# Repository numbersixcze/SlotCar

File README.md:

# SlotCar
School project - gyroscope driven slot car

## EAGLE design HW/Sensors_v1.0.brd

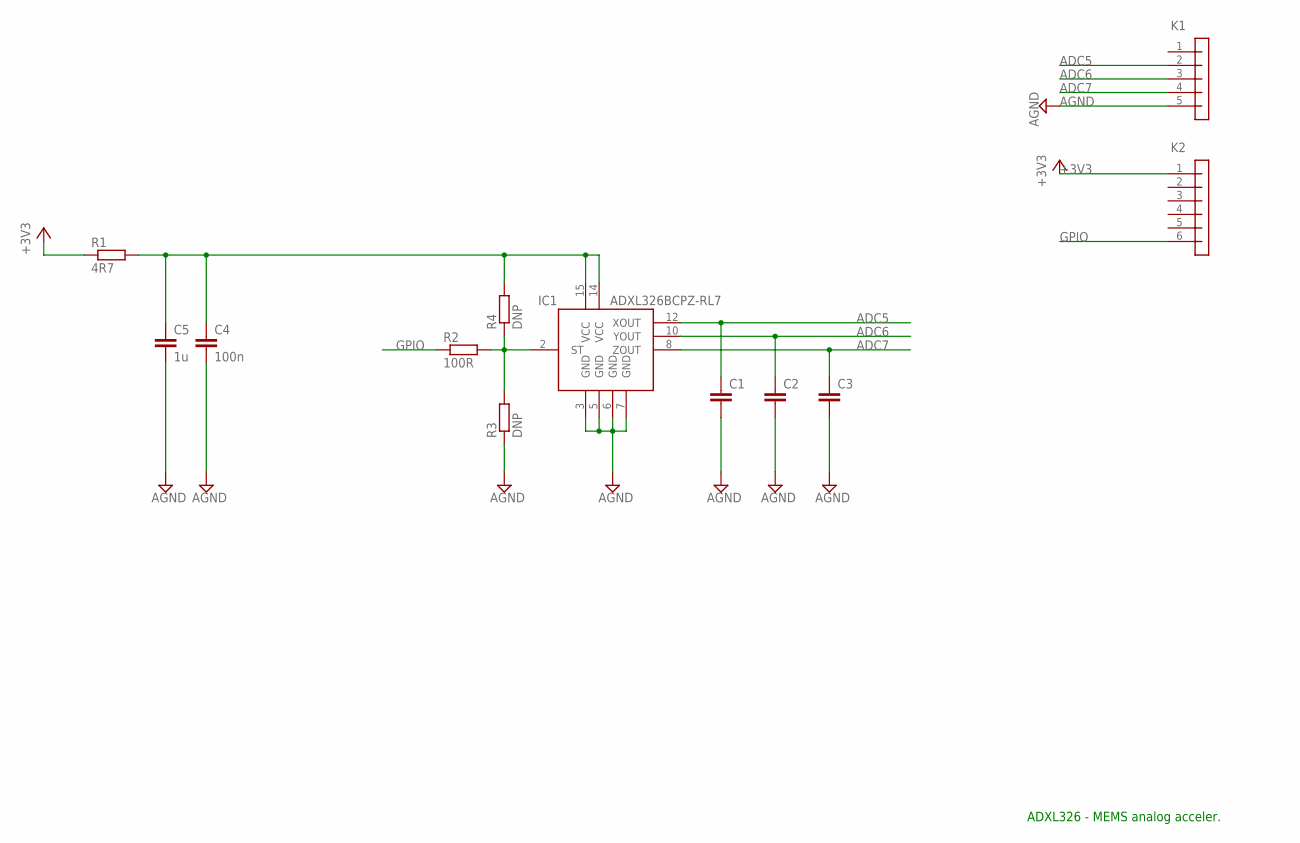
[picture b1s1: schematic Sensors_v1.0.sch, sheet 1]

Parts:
C1, C2, C3: C-EUC0805K; C0805K
C4: 100n; C0805K
C5: 1u; C0805K
IC1: ADXL326BCPZ-RL7; LFCSP-LQ-16
K1: PIN_1X5_1.27THT; PINHEAD_1X5_RM1.27THT
K2: PIN_1X6_1.27THT; PINHEAD_1X6_RM1.27THT
R1: 4R7; M0805
R2: 100R; M0805
R3, R4: DNP; M0805

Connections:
+3V3: K2.1, R1.1; also elsewhere on the board
ADC5: C1.1, IC1.12 (XOUT), K1.2; also elsewhere on the board
ADC6: C2.1, IC1.10 (YOUT), K1.3; also elsewhere on the board
ADC7: C3.1, IC1.8 (ZOUT), K1.4; also elsewhere on the board
AGND: C1.2, C2.2, C3.2, C4.2, C5.2, IC1.3 (GND), IC1.5 (GND), IC1.6 (GND), IC1.7 (GND), K1.5, R3.1; also elsewhere on the board
GPIO: K2.6, R2.1; also elsewhere on the board
unnamed: C4.1, C5.1, IC1.14 (VCC), IC1.15 (VCC), R1.2, R4.2
unnamed: IC1.2 (ST), R2.2, R3.2, R4.1

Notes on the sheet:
ADXL326 - MEMS analog acceler.

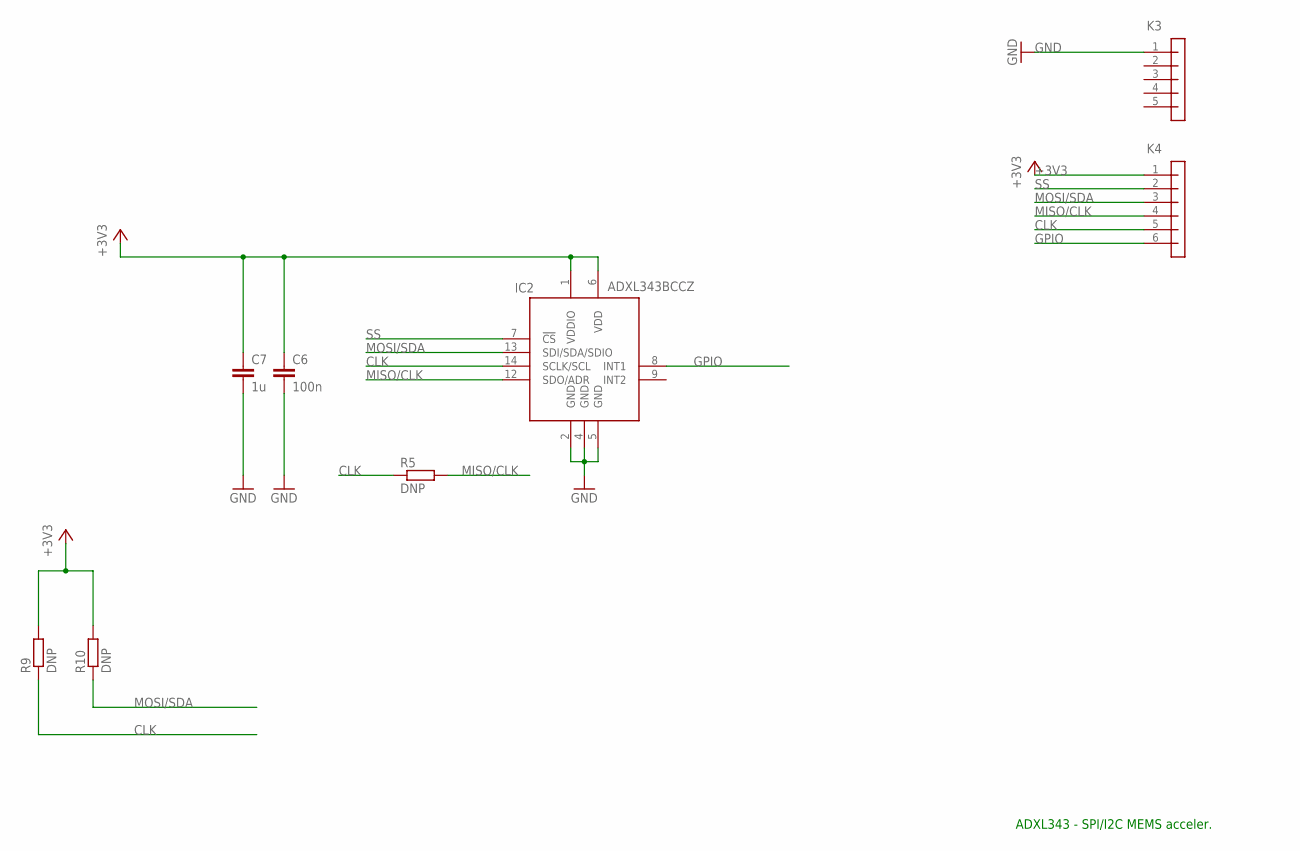
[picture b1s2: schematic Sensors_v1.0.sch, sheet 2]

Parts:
C6: 100n; C0805K
C7: 1u; C0805K
IC2: ADXL343BCCZ; LGA14(CC-14-1)
K3: PIN_1X5_1.27THT; PINHEAD_1X5_RM1.27THT
K4: PIN_1X6_1.27THT; PINHEAD_1X6_RM1.27THT
R5, R9, R10: DNP; M0805

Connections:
+3V3: C6.1, C7.1, IC2.1 (VDDIO), IC2.6 (VDD), K4.1, R9.2, R10.2; also elsewhere on the board
CLK: IC2.14 (SCLK/SCL), K4.5, R5.1, R9.1; also elsewhere on the board
GND: C6.2, C7.2, IC2.2 (GND), IC2.4 (GND), IC2.5 (GND), K3.1; also elsewhere on the board
GPIO: IC2.8 (INT1), K4.6; also elsewhere on the board
MISO/CLK: IC2.12 (SDO/ADR), K4.4, R5.2; also elsewhere on the board
MOSI/SDA: IC2.13 (SDI/SDA/SDIO), K4.3, R10.1; also elsewhere on the board
SS: IC2.7 (!CS), K4.2; also elsewhere on the board

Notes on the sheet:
ADXL343 - SPI/I2C MEMS acceler.

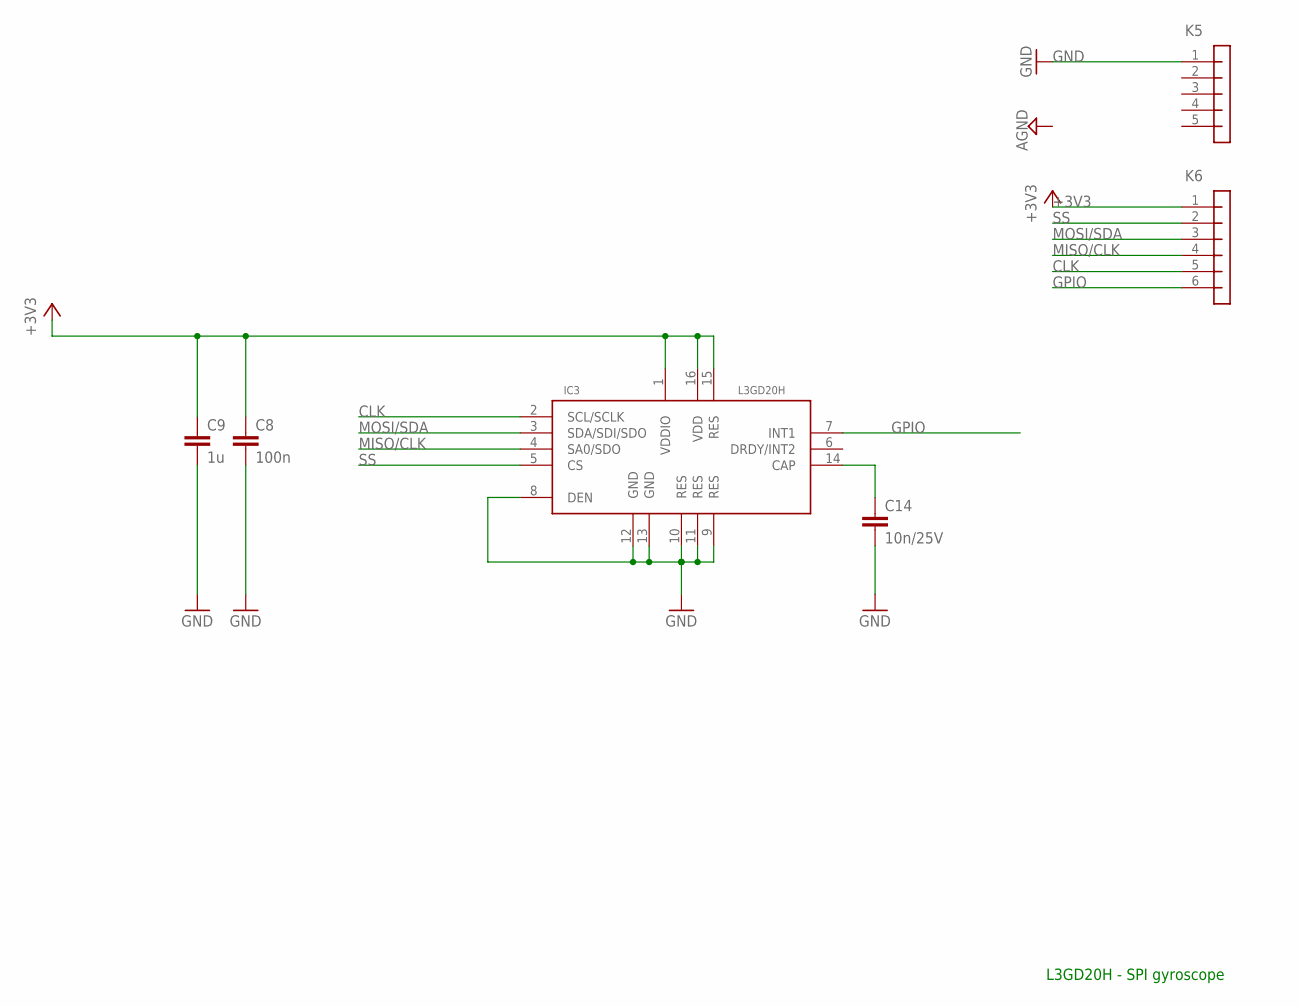
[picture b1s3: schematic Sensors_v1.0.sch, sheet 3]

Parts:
C8: 100n; C0805K
C9: 1u; C0805K
C14: 10n/25V; C0805K
IC3: L3GD20H; LGA16L
K5: PIN_1X5_1.27THT; PINHEAD_1X5_RM1.27THT
K6: PIN_1X6_1.27THT; PINHEAD_1X6_RM1.27THT

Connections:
+3V3: C8.1, C9.1, IC3.1 (VDDIO), IC3.15 (RES), IC3.16 (VDD), K6.1; also elsewhere on the board
CLK: IC3.2 (SCL/SCLK), K6.5; also elsewhere on the board
GND: C8.2, C9.2, C14.2, IC3.8 (DEN), IC3.9 (RES), IC3.10 (RES), IC3.11 (RES), IC3.12 (GND), IC3.13 (GND), K5.1; also elsewhere on the board
GPIO: IC3.7 (INT1), K6.6; also elsewhere on the board
MISO/CLK: IC3.4 (SA0/SDO), K6.4; also elsewhere on the board
MOSI/SDA: IC3.3 (SDA/SDI/SDO), K6.3; also elsewhere on the board
unnamed: C14.1, IC3.14 (CAP)
SS: IC3.5 (CS), K6.2; also elsewhere on the board

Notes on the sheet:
L3GD20H - SPI gyroscope

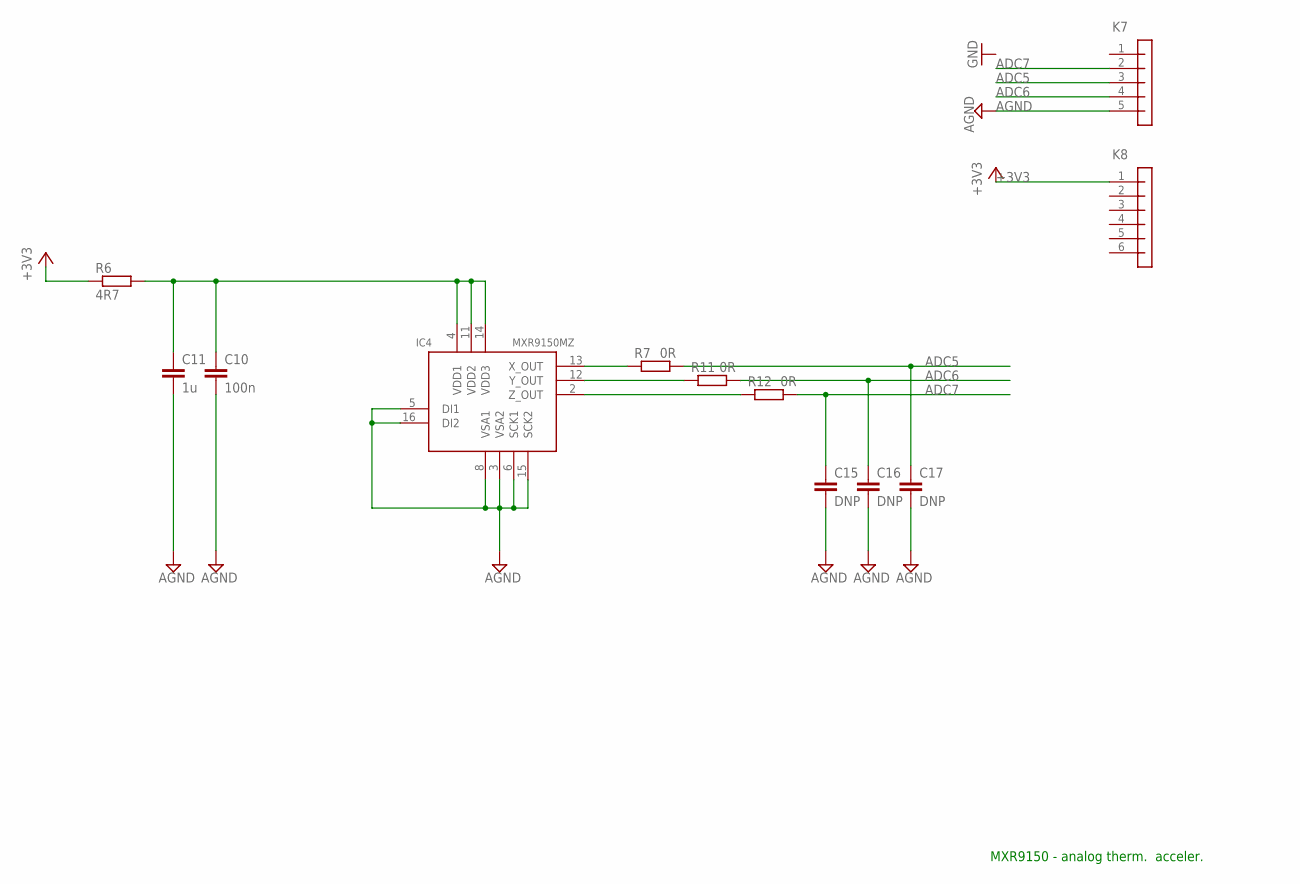
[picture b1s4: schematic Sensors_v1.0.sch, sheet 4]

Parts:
C10: 100n; C0805K
C11: 1u; C0805K
C15, C16, C17: DNP; C0805K
IC4: MXR9150MZ; LCC16
K7: PIN_1X5_1.27THT; PINHEAD_1X5_RM1.27THT
K8: PIN_1X6_1.27THT; PINHEAD_1X6_RM1.27THT
R6: 4R7; M0805
R7, R11, R12: 0R; M0805

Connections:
+3V3: K8.1, R6.1; also elsewhere on the board
ADC5: C17.1, K7.3, R7.2; also elsewhere on the board
ADC6: C16.1, K7.4, R11.2; also elsewhere on the board
ADC7: C15.1, K7.2, R12.2; also elsewhere on the board
AGND: C10.2, C11.2, C15.2, C16.2, C17.2, IC4.3 (VSA2), IC4.5 (DI1), IC4.6 (SCK1), IC4.8 (VSA1), IC4.15 (SCK2), IC4.16 (DI2), K7.5; also elsewhere on the board
unnamed: C10.1, C11.1, IC4.4 (VDD1), IC4.11 (VDD2), IC4.14 (VDD3), R6.2
unnamed: IC4.13 (X_OUT), R7.1
unnamed: IC4.12 (Y_OUT), R11.1
unnamed: IC4.2 (Z_OUT), R12.1

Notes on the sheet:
MXR9150 - analog therm. acceler.

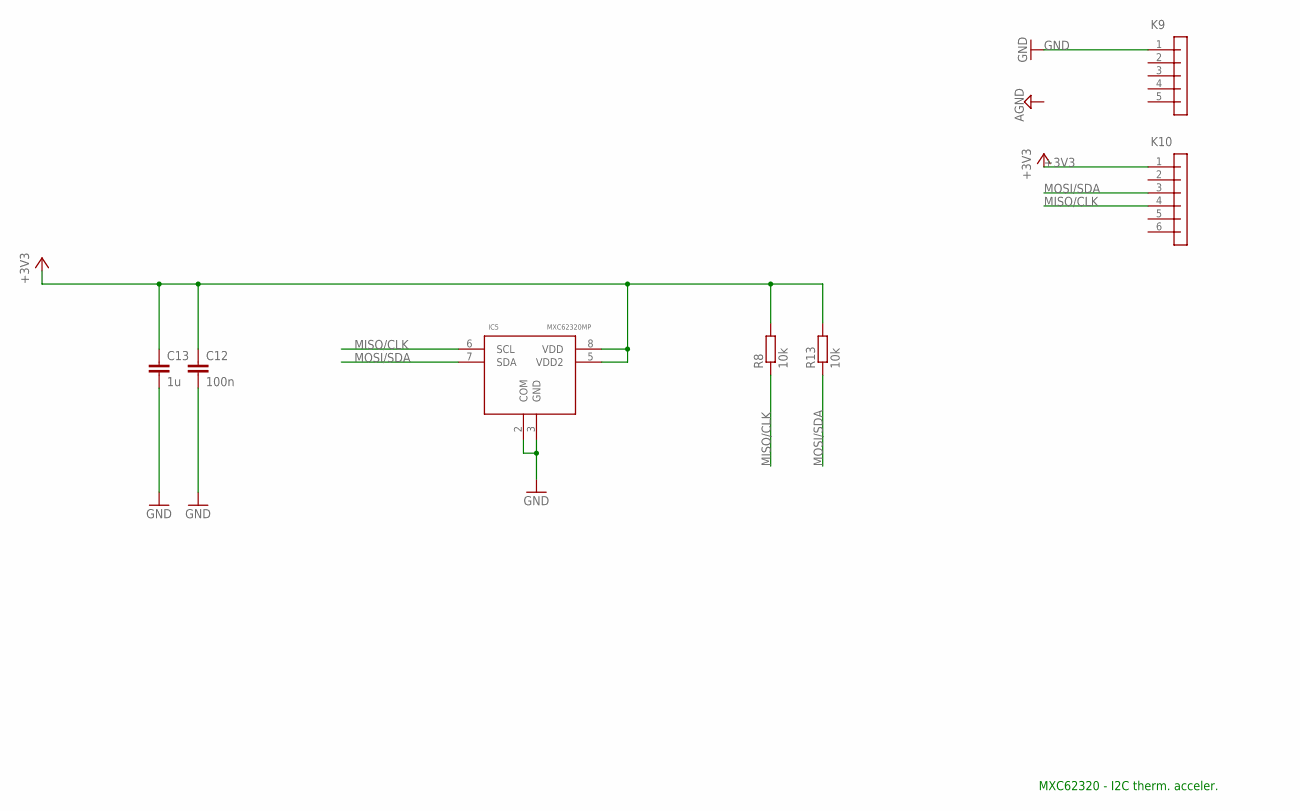
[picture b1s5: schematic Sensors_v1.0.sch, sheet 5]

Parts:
C12: 100n; C0805K
C13: 1u; C0805K
IC5: MXC62320MP; LCC8
K9: PIN_1X5_1.27THT; PINHEAD_1X5_RM1.27THT
K10: PIN_1X6_1.27THT; PINHEAD_1X6_RM1.27THT
R8, R13: 10k; M0805

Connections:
+3V3: C12.1, C13.1, IC5.5 (VDD2), IC5.8 (VDD), K10.1, R8.2, R13.2; also elsewhere on the board
GND: C12.2, C13.2, IC5.2 (COM), IC5.3 (GND), K9.1; also elsewhere on the board
MISO/CLK: IC5.6 (SCL), K10.4, R8.1; also elsewhere on the board
MOSI/SDA: IC5.7 (SDA), K10.3, R13.1; also elsewhere on the board

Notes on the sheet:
MXC62320 - I2C therm. acceler.

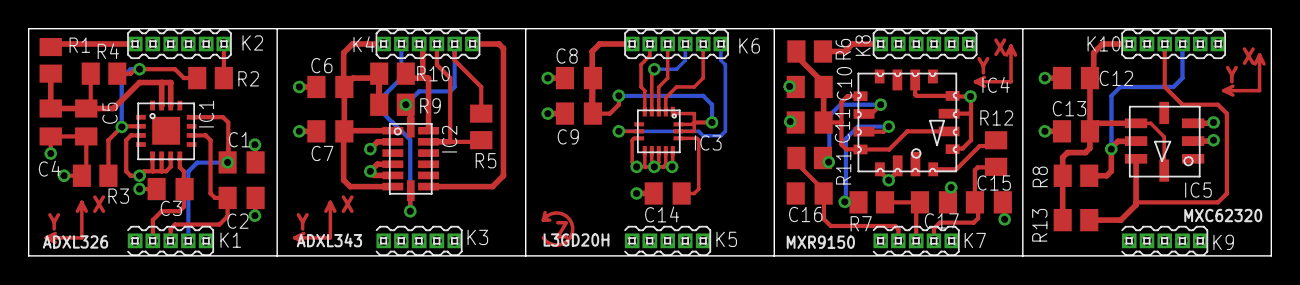
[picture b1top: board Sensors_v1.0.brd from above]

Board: 2 copper layers, 88.9 x 16.3 mm, 45 parts (0 on the bottom side), 18 nets.

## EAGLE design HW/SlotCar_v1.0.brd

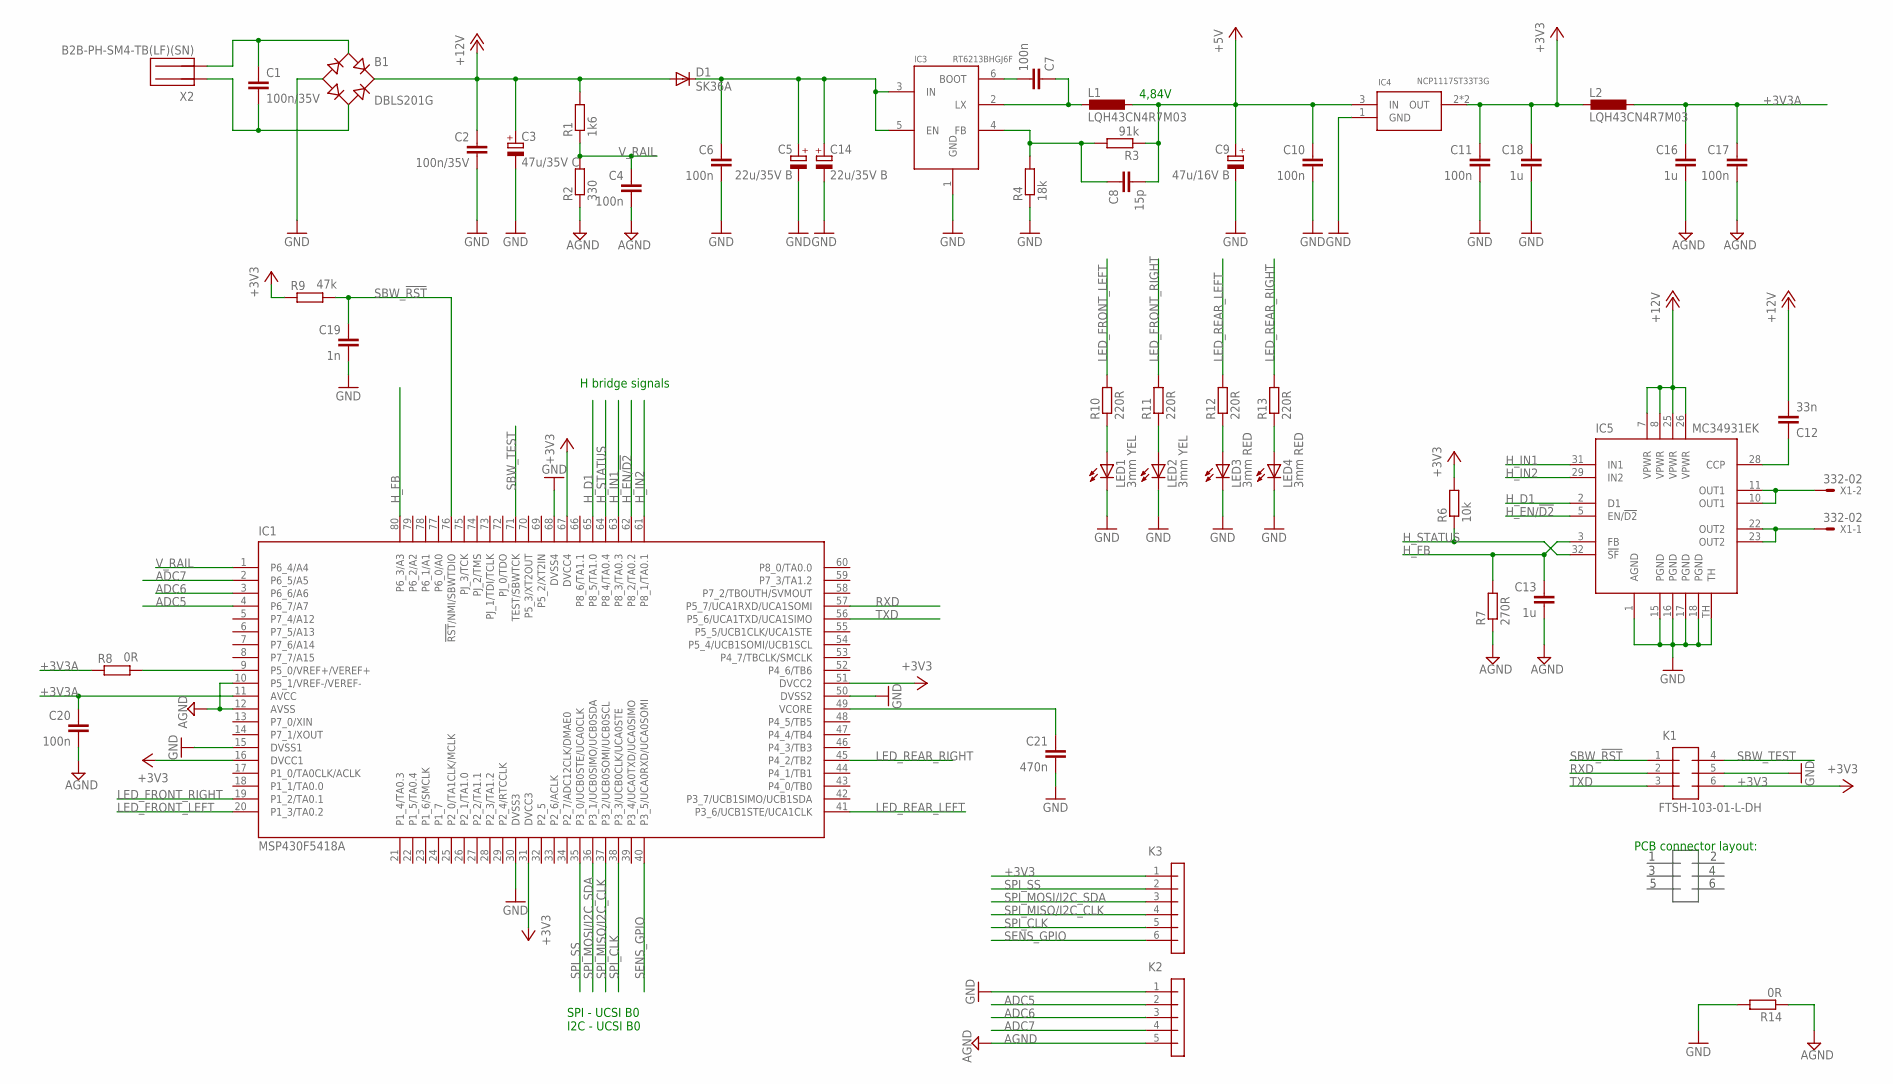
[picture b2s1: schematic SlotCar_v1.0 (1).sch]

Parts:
B1: DBLS201G; DBS
C1, C2: 100n/35V; C0805K
C3: 47u/35V C; 153CLV-0505
C4, C6, C7, C10, C11, C17, C20: 100n; C0805K
C5, C14: 22u/35V B; 153CLV-0405
C8: 15p; C0805K
C9: 47u/16V B; 153CLV-0405
C12: 33n; C0805K
C13, C16, C18: 1u; C0805K
C19: 1n; C0805K
C21: 470n; C0805K
D1: SK36A; DO214AC
IC1: MSP430F5418A; PN_S-PQFP-G80
IC3: RT6213BHGJ6F; SOT23-6
IC4: NCP1117ST33T3G; SOT223
IC5: MC34931EK; SOIC32W
K1: FTSH-103-01-L-DH; PINHEAD_2X3_RM1.27
K2: PIN_1X5_SMD; PINHEAD_1X5_RM1.27SMD
K3: PIN_1X6_SMD; PINHEAD_1X6_RM1.27SMD
L1, L2: LQH43CN4R7M03; L1812
LED1, LED2: 3mm YEL; LED3MM
LED3, LED4: 3mm RED; LED3MM
R1: 1k6; M0805
R2: 330; M0805
R3: 91k; M0805
R4: 18k; M0805
R6: 10k; M0805
R7: 270R; M0805
R8, R14: 0R; M0805
R9: 47k; M0805
R10, R11, R12, R13: 220R; M0805
X1: 332-02
X2: B2B-PH-SM4-TB(LF)(SN); JST-2.00MM-2P

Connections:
+3V3: C11.1, C18.1, IC1.16 (DVCC1), IC1.31 (DVCC3), IC1.51 (DVCC2), IC1.67 (DVCC4), IC4.2 (OUT), IC4.4 (OUT), K1.6, K3.1, L2.2, R6.2, R9.1
+3V3A: C16.1, C17.1, C20.1, IC1.11 (AVCC), L2.1, R8.1
+5V: C8.2, C9.+, C10.1, IC4.3 (IN), L1.1, R3.1
+12V: B1.+, C2.1, C3.+, C12.2, D1.A, IC5.7 (VPWR), IC5.8 (VPWR), IC5.25 (VPWR), IC5.26 (VPWR), R1.2
ADC5: IC1.4 (P6_7/A7), K2.2
ADC6: IC1.3 (P6_6/A6), K2.3
ADC7: IC1.2 (P6_5/A5), K2.4
AGND: C4.2, C13.2, C16.2, C17.2, C20.2, IC1.10 (P5_1/VREF-/VEREF-), IC1.12 (AVSS), K2.5, R2.1, R7.1, R14.1
GND: B1.-, C2.2, C3.-, C5.-, C6.2, C9.-, C10.2, C11.2, C14.-, C18.2, C19.2, C21.2, IC1.15 (DVSS1), IC1.30 (DVSS3), IC1.50 (DVSS2), IC1.68 (DVSS4), IC3.1 (GND), IC4.1 (GND), IC5.1 (AGND), IC5.15 (PGND), IC5.16 (PGND), IC5.17 (PGND), IC5.18 (PGND), IC5.TH, K1.5, K2.1, LED1.K (C), LED2.K (C), LED3.K (C), LED4.K (C), R4.1, R14.2
H_D1: IC1.65 (P8_5/TA1.0), IC5.2 (D1)
H_EN/!D2: IC1.62 (P8_2/TA0.2), IC5.5 (EN/!D2)
H_FB: C13.1, IC1.80 (P6_3/A3), IC5.3 (FB), R7.2
H_IN1: IC1.63 (P8_3/TA0.3), IC5.31 (IN1)
H_IN2: IC1.61 (P8_1/TA0.1), IC5.29 (IN2)
H_STATUS: IC1.64 (P8_4/TA0.4), IC5.32 (!SF), R6.1
LED_FRONT_LEFT: IC1.20 (P1_3/TA0.2), R10.2
LED_FRONT_RIGHT: IC1.19 (P1_2/TA0.1), R11.2
LED_REAR_LEFT: IC1.41 (P3_6/UCB1STE/UCA1CLK), R12.2
LED_REAR_RIGHT: IC1.45 (P4_2/TB2), R13.2
unnamed: IC5.10 (OUT1), IC5.11 (OUT1), X1.2
unnamed: B1.AC2, C1.2, X2.1
unnamed: B1.AC1, C1.1, X2.2
unnamed: IC5.22 (OUT2), IC5.23 (OUT2), X1.1
unnamed: C12.1, IC5.28 (CCP)
unnamed: C7.2, IC3.6 (BOOT)
unnamed: C7.1, IC3.2 (LX), L1.2
unnamed: C8.1, IC3.4 (FB), R3.2, R4.2
unnamed: LED1.A, R10.1
unnamed: IC1.9 (P5_0/VREF+/VEREF+), R8.2
unnamed: LED2.A, R11.1
unnamed: LED3.A, R12.1
unnamed: LED4.A, R13.1
unnamed: C21.1, IC1.49 (VCORE)
unnamed: C5.+, C6.1, C14.+, D1.C, IC3.3 (IN), IC3.5 (EN)
RXD: IC1.57 (P5_7/UCA1RXD/UCA1SOMI), K1.2
SBW_!RST: C19.1, IC1.76 (!RST!/NMI/SBWTDIO), K1.1, R9.2
SBW_TEST: IC1.71 (TEST/SBWTCK), K1.4
SENS_GPIO: IC1.40 (P3_5/UCA0RXD/UCA0SOMI), K3.6
SPI_CLK: IC1.38 (P3_3/UCB0CLK/UCA0STE), K3.5
SPI_MISO/I2C_CLK: IC1.37 (P3_2/UCB0SOMI/UCB0SCL), K3.4
SPI_MOSI/I2C_SDA: IC1.36 (P3_1/UCB0SIMO/UCB0SDA), K3.3
SPI_SS: IC1.35 (P3_0/UCB0STE/UCA0CLK), K3.2
TXD: IC1.56 (P5_6/UCA1TXD/UCA1SIMO), K1.3
V_RAIL: C4.1, IC1.1 (P6_4/A4), R1.1, R2.2

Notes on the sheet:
4,84V
SPI - UCSI B0 I2C - UCSI B0
H bridge signals
PCB connector layout:

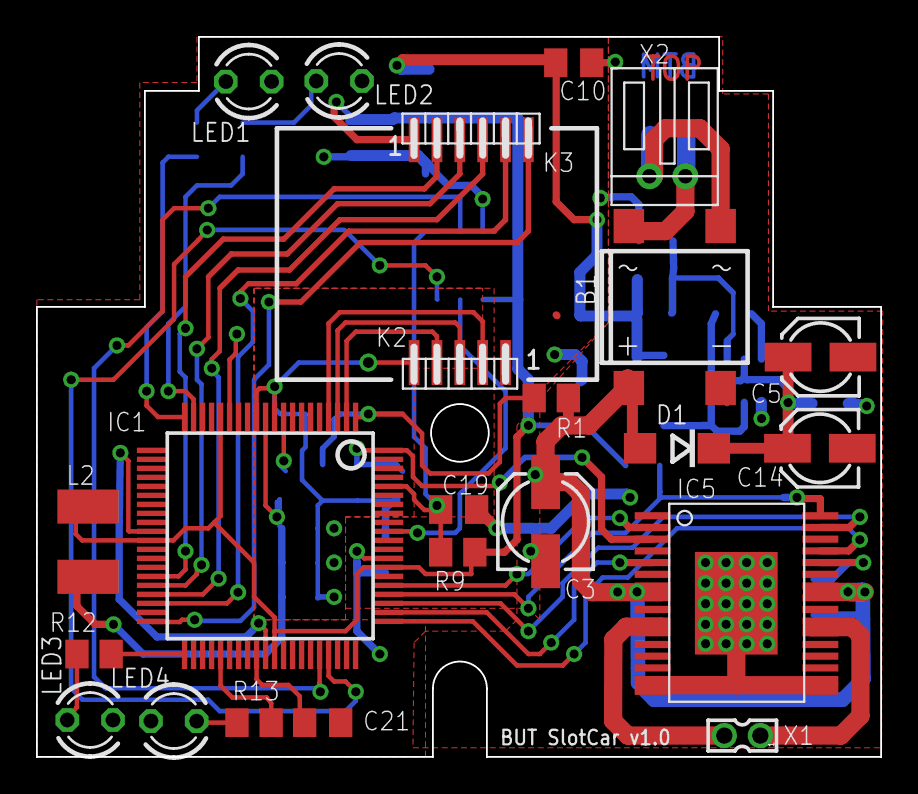
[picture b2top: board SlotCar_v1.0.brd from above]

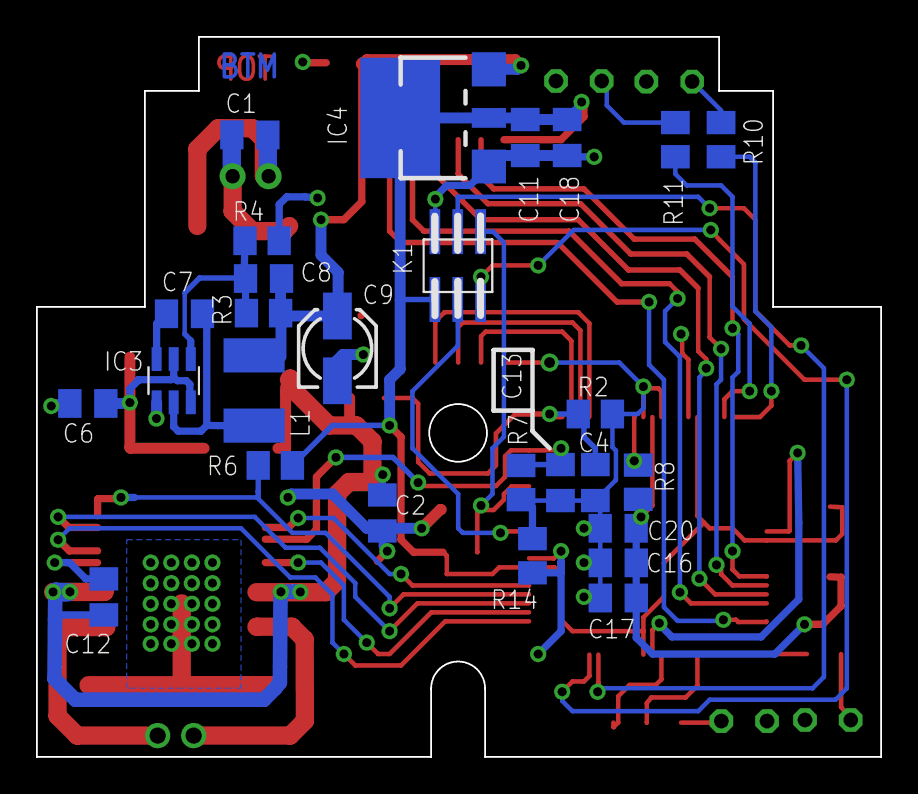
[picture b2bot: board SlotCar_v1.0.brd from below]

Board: 2 copper layers, 46.9 x 40.0 mm, 50 parts (27 on the bottom side), 44 nets.

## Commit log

2019-10-17 Aktualizace
2019-11-07 update nefunkcni
2019-11-20 odevdani txt
2019-11-28 ono to KURWA funguje
2019-12-04 Relativne funkcni jizda s akvizicí
